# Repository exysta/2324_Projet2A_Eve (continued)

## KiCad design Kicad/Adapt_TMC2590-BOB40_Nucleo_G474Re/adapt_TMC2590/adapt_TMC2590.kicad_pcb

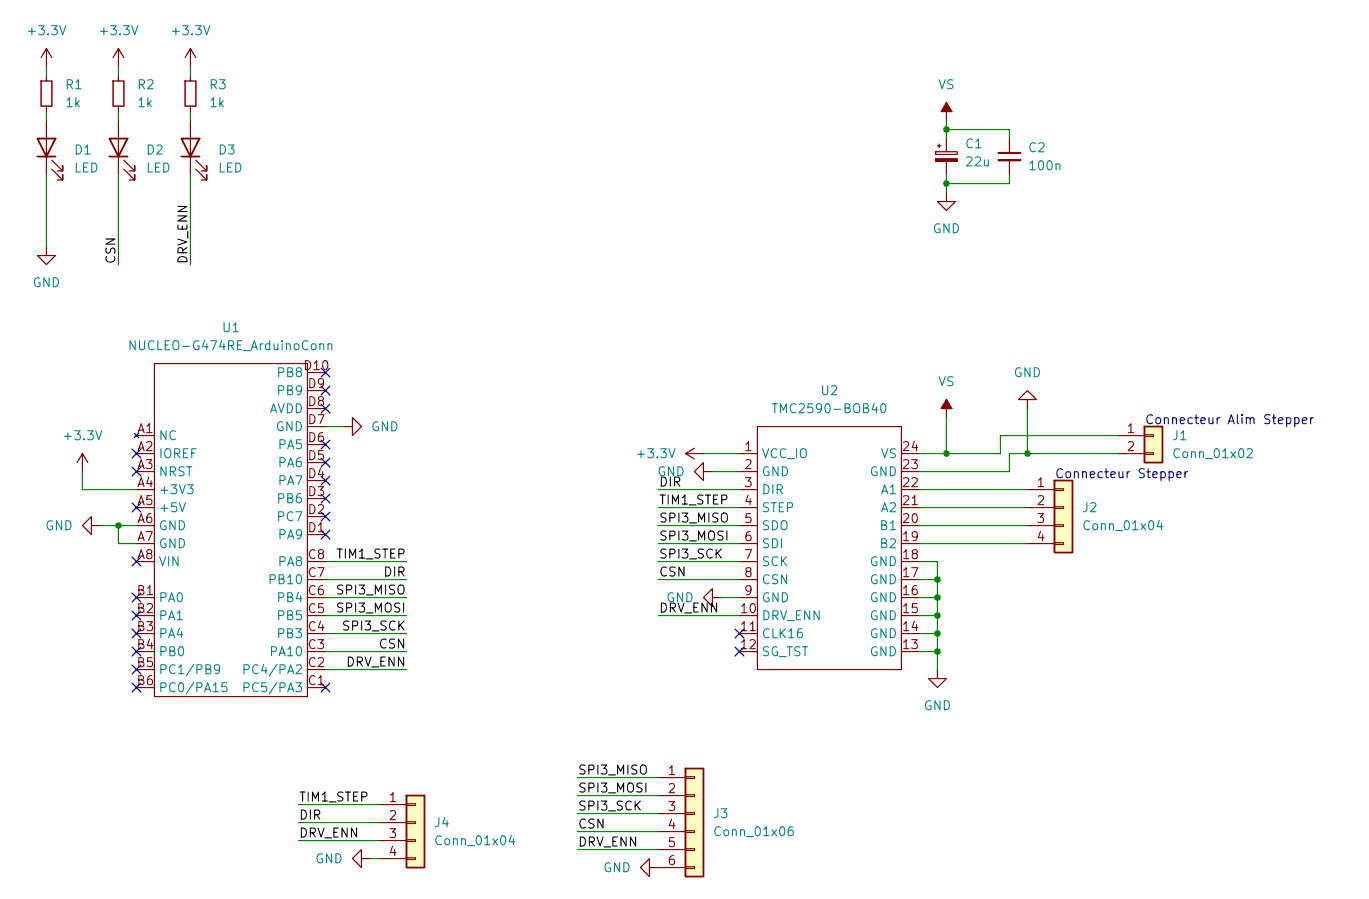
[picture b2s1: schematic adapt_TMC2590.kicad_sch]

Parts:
C1: 22u; CP_Elec_6.3x5.4
C2: 100n; C_0603_1608Metric_Pad1.08x0.95mm_HandSolder
D1, D2, D3: LED; LED_0603_1608Metric_Pad1.05x0.95mm_HandSolder
J1: Conn_01x02; JST_XH_S2B-XH-A_1x02_P2.50mm_Horizontal
J2: Conn_01x04; JST_XH_S4B-XH-A_1x04_P2.50mm_Horizontal
J3: Conn_01x06; PinHeader_1x06_P2.54mm_Vertical
J4: Conn_01x04; PinHeader_1x04_P2.54mm_Vertical
R1, R2, R3: 1k; R_0603_1608Metric_Pad0.98x0.95mm_HandSolder
U1: NUCLEO-G474RE_ArduinoConn; Nucleo-G474RE_ArduinoConn
U2: TMC2590-BOB40

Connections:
+3.3V: R1.1, R2.1, R3.1, U1.A4 (+3V3), U2.1 (VCC_IO)
/CSN: D2.1 (K), J3.4, U1.C3 (PA10), U2.8 (CSN)
/DIR: J4.2, U1.C7 (PB10), U2.3 (DIR)
/DRV_ENN: D3.1 (K), J3.5, J4.3, U1.C2 (PC4/PA2), U2.10 (DRV_ENN)
/SPI3_MISO: J3.1, U1.C6 (PB4), U2.5 (SDO)
/SPI3_MOSI: J3.2, U1.C5 (PB5), U2.6 (SDI)
/SPI3_SCK: J3.3, U1.C4 (PB3), U2.7 (SCK)
/TIM1_STEP: J4.1, U1.C8 (PA8), U2.4 (STEP)
GND: C1.2, C2.2, D1.1 (K), J1.2, J3.6, J4.4, U1.A6 (GND), U1.A7 (GND), U1.D7 (GND), U2.2 (GND), U2.9 (GND), U2.13 (GND), U2.14 (GND), U2.15 (GND), U2.16 (GND), U2.17 (GND), U2.18 (GND), U2.23 (GND)
unnamed: D1.2 (A), R1.2
unnamed: D2.2 (A), R2.2
unnamed: D3.2 (A), R3.2
unnamed: J2.1, U2.22 (A1)
unnamed: J2.2, U2.21 (A2)
unnamed: J2.3, U2.20 (B1)
unnamed: J2.4, U2.19 (B2)
VS: C1.1, C2.1, J1.1, U2.24 (VS)

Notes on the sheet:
Connecteur Alim Stepper
Connecteur Stepper

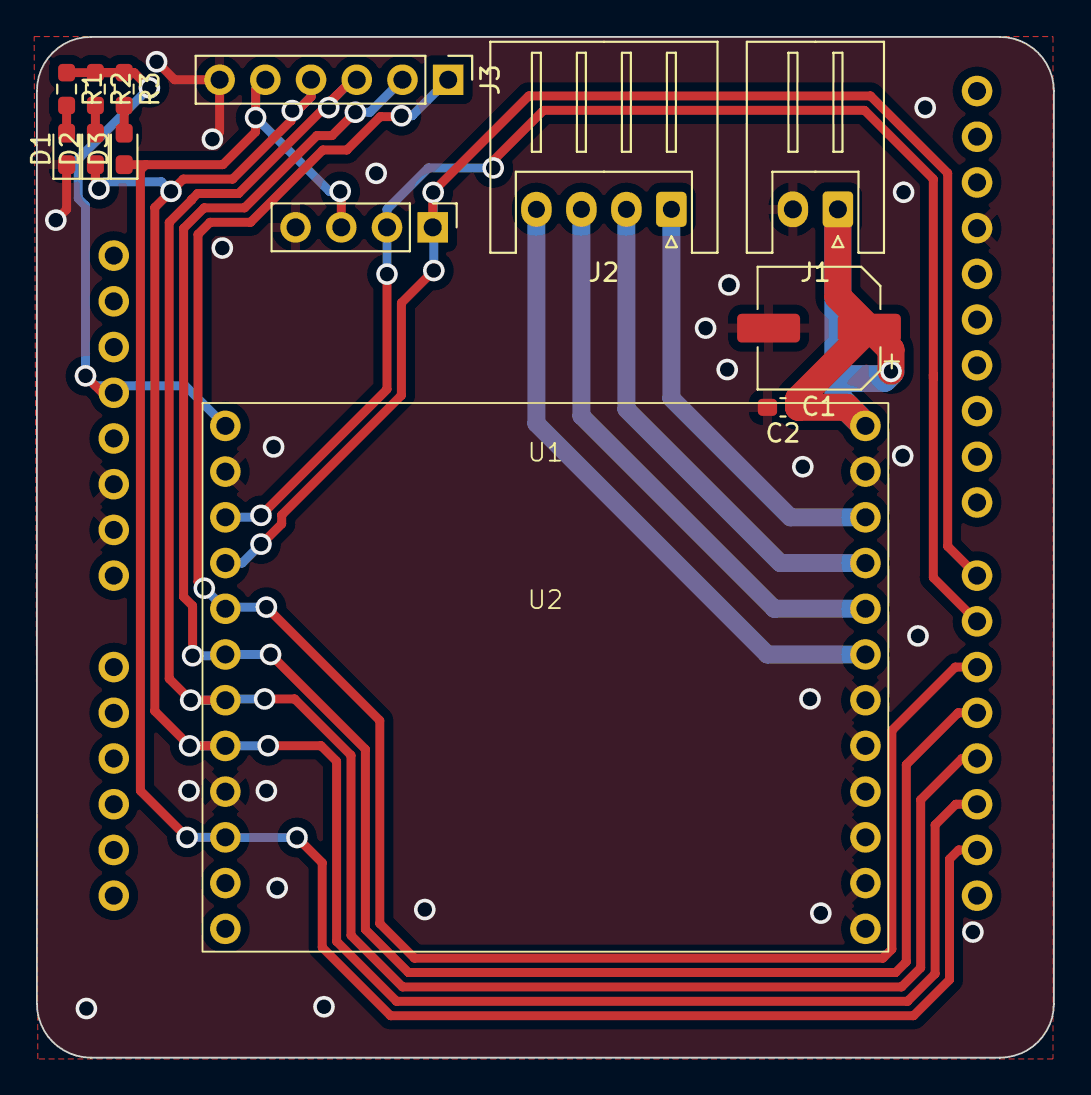
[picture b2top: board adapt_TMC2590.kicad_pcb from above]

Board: 2 copper layers, 56.5 x 56.7 mm, 14 parts (0 on the bottom side), 17 nets.

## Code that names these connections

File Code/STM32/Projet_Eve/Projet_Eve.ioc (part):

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Mcu.Name=STM32U535RETx
Mcu.Package=LQFP64
Mcu.UserName=STM32U535RETx
PA0.GPIOParameters=GPIO_Label
PA0.GPIO_Label=ST_LINK_TX
PA0.Mode=Asynchronous
PA0.Signal=UART4_TX
PA1.GPIOParameters=GPIO_Label
PA1.GPIO_Label=ST_LINK_RX
PA1.Mode=Asynchronous
PA1.Signal=UART4_RX
PA10.GPIOParameters=GPIO_Label
PA10.GPIO_Label=USR_LED_3
PA10.Signal=GPIO_Output
PA11.GPIOParameters=GPIO_Label
PA11.GPIO_Label=USR_LED_4
PA11.Signal=GPIO_Output
PA13\ (JTMS/SWDIO).Signal=DEBUG_JTMS-SWDIO
PA14\ (JTCK/SWCLK).Signal=DEBUG_JTCK-SWCLK
PA4.GPIOParameters=GPIO_Label
PA4.GPIO_Label=FDC_1
PA4.Signal=GPIO_Input
PA5.GPIOParameters=GPIO_Label
PA5.GPIO_Label=FDC_4
PA5.Signal=GPIO_Input
PA6.GPIOParameters=GPIO_Label
PA6.GPIO_Label=FDC_5
PA6.Signal=GPIO_Input
PA7.GPIOParameters=GPIO_Label
PA7.GPIO_Label=FDC_2
PA7.Signal=GPIO_Input
PA8.GPIOParameters=GPIO_Label
PA8.GPIO_Label=USR_LED_1
PA8.Signal=GPIO_Output
PA9.GPIOParameters=GPIO_Label
PA9.GPIO_Label=USR_LED_2
PA9.Signal=GPIO_Output
PB0.GPIOParameters=GPIO_Label
PB0.GPIO_Label=FDC_7
PB0.Signal=GPIO_Input
PB1.GPIOParameters=GPIO_Label
PB1.GPIO_Label=FDC_6
PB1.Signal=GPIO_Input
PB13.Mode=Full_Duplex_Master
PB13.Signal=SPI2_SCK
PB14.Mode=Full_Duplex_Master
PB14.Signal=SPI2_MISO
PB15.Mode=Full_Duplex_Master
PB15.Signal=SPI2_MOSI
PB3\ (JTDO/TRACESWO).Signal=DEBUG_JTDO-SWO
PB6.GPIOParameters=GPIO_Speed,GPIO_PuPd,GPIO_Label,GPIO_ModeDefaultOD
PB6.GPIO_Label=Servos
PB6.GPIO_ModeDefaultOD=GPIO_MODE_AF_OD
PB6.GPIO_PuPd=GPIO_PULLUP
PB6.GPIO_Speed=GPIO_SPEED_FREQ_VERY_HIGH
PB6.Mode=Half_duplex(single_wire_mode)
PB6.Signal=USART1_TX
PC0.GPIOParameters=GPIO_Label
PC0.GPIO_Label=Rasp_RX
PC0.Mode=Asynchronous
PC0.Signal=LPUART1_RX
PC1.GPIOParameters=GPIO_Label
PC1.GPIO_Label=Rasp_TX
PC1.Mode=Asynchronous
PC1.Signal=LPUART1_TX
PC10.GPIOParameters=GPIO_Label
PC10.GPIO_Label=USR_BTN_2
PC10.Signal=GPIO_Input
PC11.GPIOParameters=GPIO_Label
PC11.GPIO_Label=USR_BTN_3
PC11.Signal=GPIO_Input
PC12.GPIOParameters=GPIO_Label
PC12.GPIO_Label=USR_BTN_1
PC12.Signal=GPIO_Input
PC4.GPIOParameters=GPIO_Label
PC4.GPIO_Label=FDC_3
PC4.Signal=GPIO_Input
PC5.GPIOParameters=GPIO_Label
PC5.GPIO_Label=FDC_8
PC5.Signal=GPIO_Input
PC6.GPIOParameters=GPIO_Label
PC6.GPIO_Label=GPIO_CSN1
PC6.Signal=GPIO_Output
PC7.GPIOParameters=GPIO_Label
PC7.GPIO_Label=GPIO_CSN1
PC7.Signal=GPIO_Output
PC8.GPIOParameters=GPIO_Label
PC8.GPIO_Label=GPIO_CSN1
PC8.Signal=GPIO_Output
PH0-OSC_IN\ (PH0).Mode=HSE-External-Oscillator
PH0-OSC_IN\ (PH0).Signal=RCC_OSC_IN
PH1-OSC_OUT\ (PH1).Mode=HSE-External-Oscillator
PH1-OSC_OUT\ (PH1).Signal=RCC_OSC_OUT
RCC.HSE_VALUE=16000000
board=custom

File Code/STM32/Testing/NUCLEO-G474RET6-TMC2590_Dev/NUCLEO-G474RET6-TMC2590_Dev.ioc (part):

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Mcu.Name=STM32G474R(B-C-E)Tx
Mcu.Package=LQFP64
Mcu.UserName=STM32G474RETx
PA10.GPIOParameters=GPIO_Label
PA10.GPIO_Label=nCS
PA10.Signal=GPIO_Output
PA13.GPIOParameters=GPIO_Label
PA13.GPIO_Label=T_SWDIO
PA13.Mode=Serial_Wire
PA13.Signal=SYS_JTMS-SWDIO
PA14.GPIOParameters=GPIO_Label
PA14.GPIO_Label=T_SWCLK
PA14.Mode=Serial_Wire
PA14.Signal=SYS_JTCK-SWCLK
PA2.GPIOParameters=GPIO_Label
PA2.GPIO_Label=LPUART1_TX [STLINKV3E_VCP_RX]
PA2.Mode=Asynchronous
PA2.Signal=LPUART1_TX
PA3.GPIOParameters=GPIO_Label
PA3.GPIO_Label=LPUART1_RX [STLINKV3E_VCP_TX]
PA3.Mode=Asynchronous
PA3.Signal=LPUART1_RX
PA5.GPIOParameters=GPIO_Label
PA5.GPIO_Label=LD2 [green led]
PA5.Signal=GPIO_Output
PA8.GPIOParameters=GPIO_Label
PA8.GPIO_Label=TIM1_STEP
PA8.Signal=S_TIM1_CH1
PB10.GPIOParameters=GPIO_Label
PB10.GPIO_Label=DIR
PB10.Signal=GPIO_Output
PB3.GPIOParameters=GPIO_Speed
PB3.GPIO_Speed=GPIO_SPEED_FREQ_VERY_HIGH
PB3.Mode=Full_Duplex_Master
PB3.Signal=SPI3_SCK
PB4.GPIOParameters=GPIO_Speed
PB4.GPIO_Speed=GPIO_SPEED_FREQ_VERY_HIGH
PB4.Mode=Full_Duplex_Master
PB4.Signal=SPI3_MISO
PB5.GPIOParameters=GPIO_Speed
PB5.GPIO_Speed=GPIO_SPEED_FREQ_HIGH
PB5.Mode=Full_Duplex_Master
PB5.Signal=SPI3_MOSI
PC13.GPIOParameters=GPIO_Label
PC13.GPIO_Label=B1 [blue push button]
PC13.Signal=GPXTI13
PC14-OSC32_IN.Mode=LSE-External-Oscillator
PC14-OSC32_IN.Signal=RCC_OSC32_IN
PC15-OSC32_OUT.Mode=LSE-External-Oscillator
PC15-OSC32_OUT.Signal=RCC_OSC32_OUT
PC4.GPIOParameters=GPIO_Label
PC4.GPIO_Label=DRV_ENN
PC4.Signal=GPIO_Output
PC8.GPIOParameters=GPIO_Label
PC8.GPIO_Label=Switch
PC8.Signal=GPIO_Input
PF0-OSC_IN.Mode=HSE-External-Oscillator
PF0-OSC_IN.Signal=RCC_OSC_IN
PF1-OSC_OUT.Mode=HSE-External-Oscillator
PF1-OSC_OUT.Signal=RCC_OSC_OUT
RCC.HSE_VALUE=24000000
RCC.SYSCLKFreq_VALUE=170000000
RCC.SYSCLKSource=RCC_SYSCLKSOURCE_PLLCLK
board=NUCLEO-G474RE
boardIOC=true

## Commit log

2023-09-19 Test
2023-09-19 Réformation du Github
2023-09-19 Create Lien_utiles
2023-09-19 Rename Lien_utiles to Lien_utiles.md
2023-09-20 Ajout du fichier fichier.txt
2023-09-20 Rm fichier.txt
2023-09-26 Ajout datasheet TMC2225
2023-09-26 Update Liens_utiles.md
    Ajouter lien tuto git/github
2023-09-26 Ajout datasheet
2023-09-26 modified code/read.md
2023-09-26 Update ReadMe.md
    je sais pas si il y a le .md à la fin du lien
2023-09-26 essai
2023-09-26 Destruction des entités inconnues
2023-10-03 Ajout dossiers
2023-10-06 Create cahier_des_charges
2023-10-08 Envoi de datasheets
2023-10-08 Add files via upload
    Ajout de la datasheet du nouveau driver TMC 2240
2023-10-09 Ajout DS TMC2590
2023-10-10 Ajout Schematic TMC2590 Plaquette essai
2023-10-10 Ajout fichiers présentation & commande
2023-10-10 Suppresion fichier inutile
2023-10-10 Ajout photo
2023-10-10 Maj*
2023-10-13 Add files via upload
    Ajout du diagramme d'architecture
2023-10-15 Nettoyage
2023-10-17 Add files via upload
    correction du diagramme d'architecture
2023-10-17 Envoi
2023-10-17 Pour présentation
2023-10-17 added KiCAd project
2023-10-24 Add files via upload
    ajout datasheet STM32U535
2023-10-24 Add files via upload
    liaison stm32-tmc2590
2023-10-24 Ajout tableau sin
2023-10-24 Ajout du code STM32
2023-11-05 Ajout images
2023-11-06 Kicad changes
2023-11-07 added stm32U5 reference manual
2023-11-08 Ajout code STM32
2023-11-10 updtated Kicad ver 7.11.23
2023-11-10 KiCad changes 10/11
2023-11-10 Kicad changes 11/11/22 added quartz
2023-11-11 added Kicad libraries to git + sch changes 11/11/23
2023-11-12 changed quartz 12/11/23
2023-11-13 changes 13/11/23
2023-11-13 empreinte 13/11
2023-11-14 Maj STM32
2023-11-14 added STM32H7A3 test code dynamixel 2.0 XL430 + notes on Dynamixel
2023-11-15 add adapt card kicad project for testing TMC2590 on Nucleo-G474RE board
2023-11-17 create project for testing TMC2590 on NUCLEO-G474RET6
2023-11-19 add sin table for tmc2590 + sending current/pol current coils
2023-11-21 USART3 working UART4 bug :)))) 21/11/2023
2023-11-23 working half-duplex USART ! crc not sure 23/11/2023
2023-11-26 Maj SPI code & Restructuration
2023-11-26 Ajout ZIP code
2023-11-28 pulled main and started routing
2023-11-28 28/11 sendOrder trigo & direct
2023-11-28 fixed + working half duplex
2023-11-30 Suppresion documentation Ax-12
2023-11-30 send dynamixel fucntion working
2023-12-01 better send functions for servo
2023-12-01 pulled last changes from charlotte
2023-12-01 latest Kicad pulled
2023-12-01 finished routing errors remain
2023-12-04 Update code SPI with commentary
2023-12-05 Update ReadMe + Code
2023-12-08 started cleaning up PCB
2023-12-08 started cleaning PCB
2023-12-09 EVE 2.0 WIP
2023-12-12 update pcb
2023-12-12 Update SPI with structures & taking positions
2023-12-12 Add Datasheet Switch
2023-12-16 PCB changes
2023-12-16 lib working for all + PCB progress
2023-12-18 ReadMe update
2023-12-18 PCB tried some layout
2023-12-18 update 18/12
2023-12-18 update 17/12
2023-12-18 PCB cleaning
2023-12-19 update 19/12
2023-12-19 update cha 19/12
2023-12-19 small PCB update
2023-12-19 Update 19/12 SPI
2023-12-20 updata cha 20/12
2023-12-20 Big PCB update errors remain
2023-12-20 fixing remaining errors
2023-12-21 correction warning
2023-12-22 pcb update
2023-12-23 Final update ?!
2023-12-23 fixed some issues on PCB
2023-12-23 small changes
2023-12-23 review PCB
2023-12-23 simply renamed a button
2024-01-23 update and finish pcb upgrade
2024-01-23 update 16/01
2024-01-23 modif cod
2024-01-23 modif code
2024-01-23 Servo driver update
2024-01-29 working HALF duplex through STLINK
2024-01-30 Remove ignored files
2024-01-30 small cleanup
2024-01-30 small cleanup v2
2024-01-31 fixing some issues
2024-02-05 added ROS2 files for STM32
2024-02-05 Micro ROS setup
2024-02-05 establishing connexion no message yet
2024-02-06 workin LEEEEDDDDDDD :)))))) git add .git add .git add .git add .
2024-02-06 working dyn2send
2024-02-06 cleaner function template dyn2
2024-02-09 fixed issues constant values
2024-02-09 initial commit for the project running on the PCB
2024-02-27 added the code for raspi
2024-02-28 Update README.md
    started Dynamixel 2.0 explanation
2024-03-05 bip boop stepper update
2024-03-05 bip bip code update
2024-03-05 merging
2024-03-05 added files for dma
2024-03-05 dynamixel update
2024-03-09 update Lucas is chafric
2024-03-09 commentaire ce que je veux
2024-03-12 position d'angles
